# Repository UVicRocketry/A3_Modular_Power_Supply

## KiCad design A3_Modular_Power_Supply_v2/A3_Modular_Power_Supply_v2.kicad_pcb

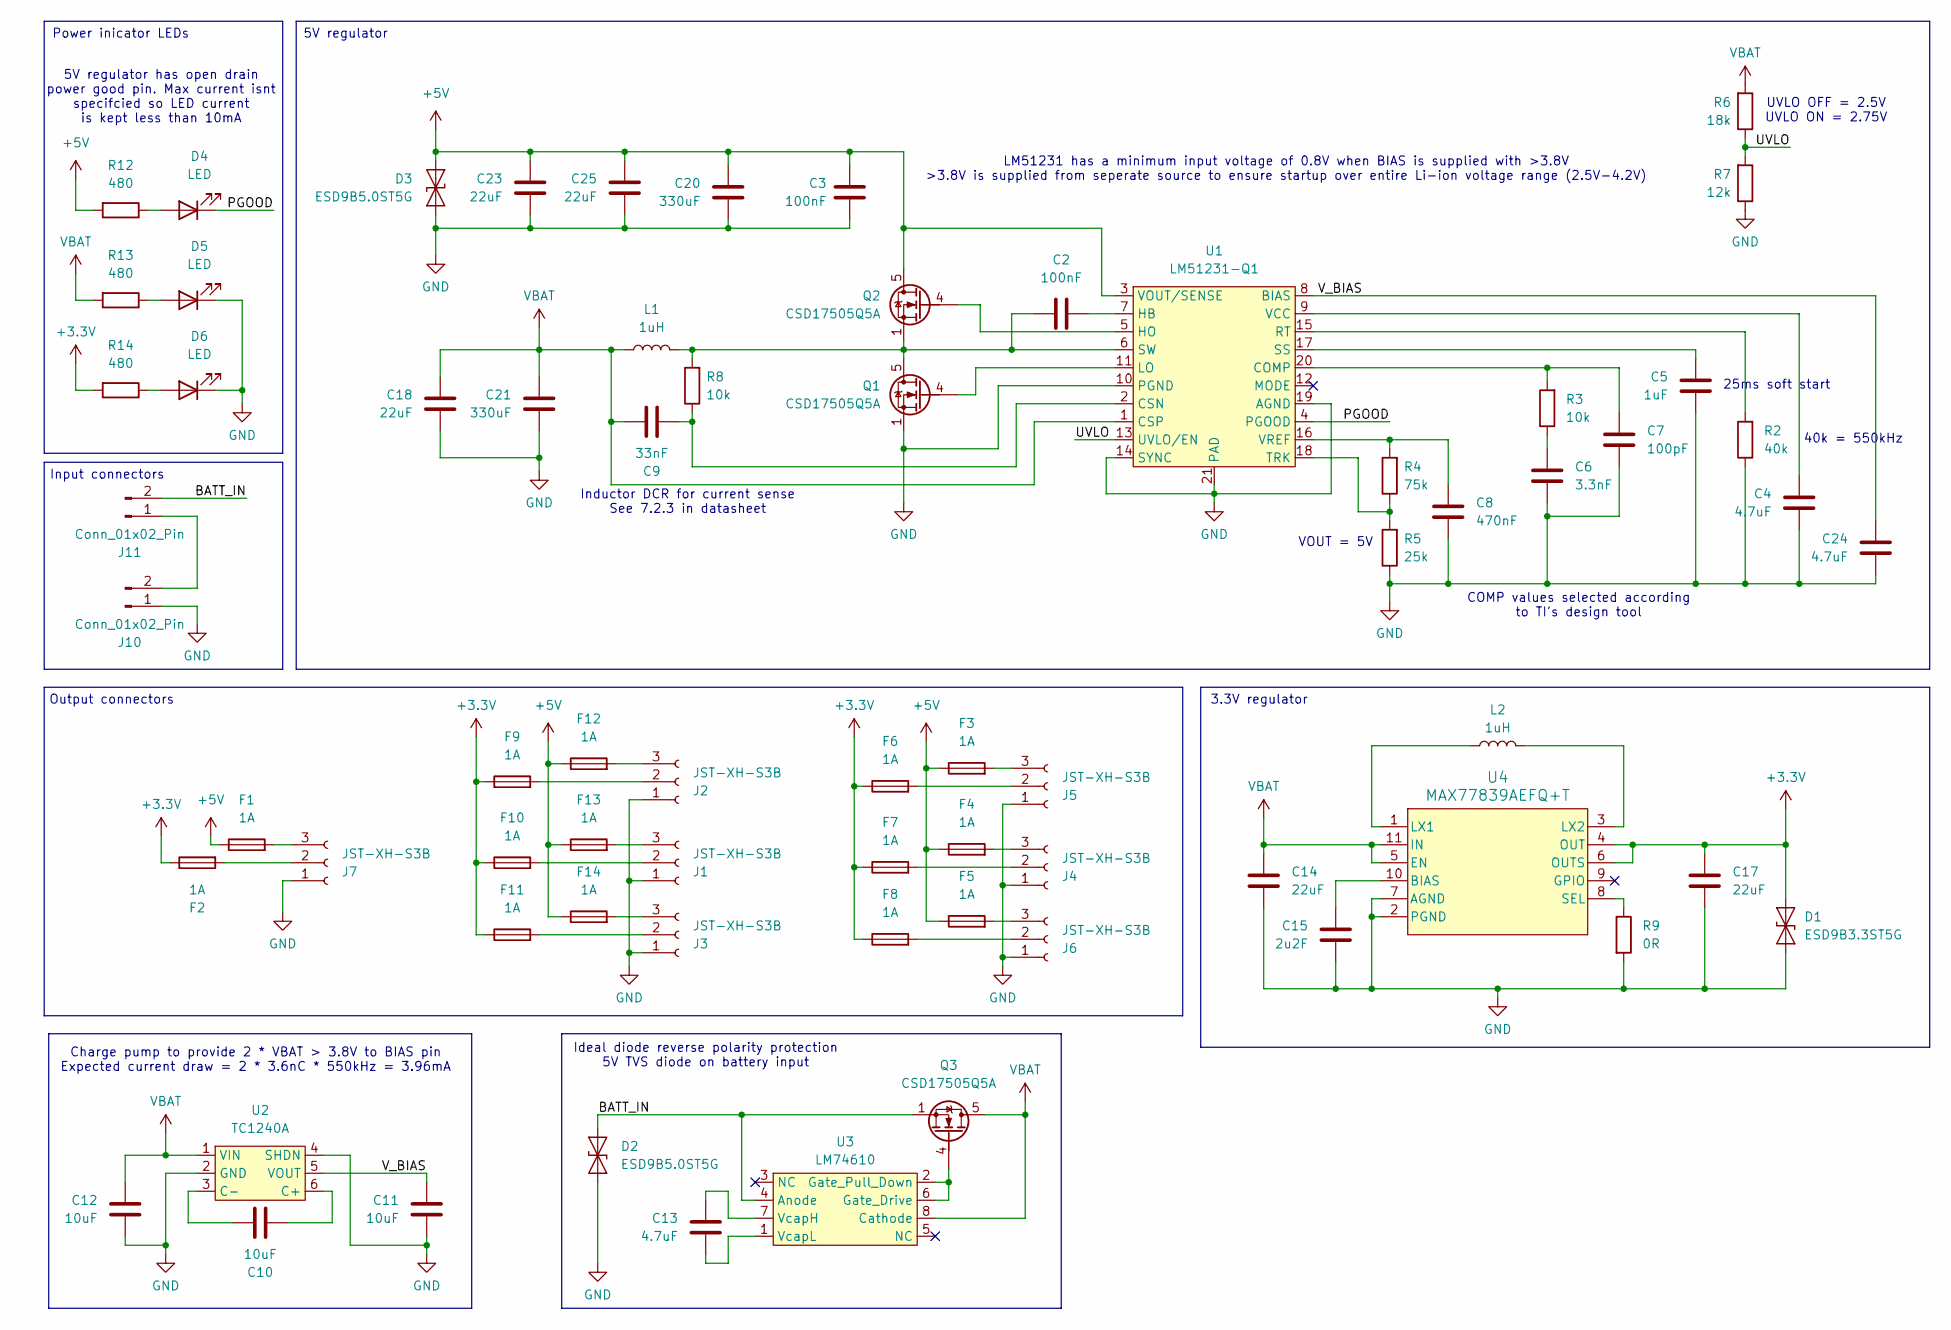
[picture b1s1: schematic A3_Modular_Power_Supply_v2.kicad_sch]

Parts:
C2, C3: 100nF; C_0402_1005Metric
C4, C13, C24: 4.7uF; C_0603_1608Metric
C5: 1uF; C_0402_1005Metric
C6: 3.3nF; C_0402_1005Metric
C7: 100pF; C_0402_1005Metric
C8: 470nF; C_0402_1005Metric
C9: 33nF; C_0402_1005Metric
C10, C11, C12: 10uF; C_0603_1608Metric
C14, C17, C18, C23, C25: 22uF; C_1210_3225Metric
C15: 2u2F; C_0603_1608Metric
C20, C21: 330uF; CP_Elec_6.3x7.7
D1: ESD9B3.3ST5G; D_SOD-923
D2, D3: ESD9B5.0ST5G; D_SOD-923
D4, D5, D6: LED; LED_0603_1608Metric
F1, F2, F3, F4, F5, F6, F7, F8, F9, F10, F11, F12, F13, F14: 1A; Fuse_0603_1608Metric
J1, J2, J3, J4, J5, J6, J7: JST-XH-S3B; JST_XH_S3B-XH-A_1x03_P2.50mm_Horizontal
J10, J11: Conn_01x02_Pin; JST_VH_B2PS-VH_1x02_P3.96mm_Horizontal
L1: 1uH; SRP1038WA
L2: 1uH; L_Wuerth_MAPI-5020
Q1, Q2, Q3: CSD17505Q5A; TDSON-8-1
R2: 40k; R_0402_1005Metric
R3, R8: 10k; R_0402_1005Metric
R4: 75k; R_0402_1005Metric
R5: 25k; R_0402_1005Metric
R6: 18k; R_0402_1005Metric
R7: 12k; R_0402_1005Metric
R9: 0R; R_0402_1005Metric
R12, R13, R14: 480; R_0402_1005Metric
U1: LM51231-Q1; QFN-20-1EP_3.5x3.5mm_P0.5mm_EP2x2mm
U2: TC1240A; TSOT-23-6
U3: LM74610; VSSOP-8_3x3mm_P0.65mm
U4: MAX77839AEFQ+T; 21-100431_F112A2F&plus_1_MXM

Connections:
+3.3V: C17.1, D1.2 (A2), F2.1, F6.1, F7.1, F8.1, F9.1, F10.1, F11.1, R14.2, U4.4 (OUT), U4.6 (OUTS)
+5V: C3.2, C20.1, C23.1, C25.1, D3.2 (A2), F1.1, F3.1, F4.1, F5.1, F12.1, F13.1, F14.1, Q2.5 (D), R12.2, U1.3 (VOUT/SENSE)
/BATT_IN: D2.2 (A2), J11.2, Q3.1 (S), Q3.2 (S), Q3.3 (S), U3.4 (Anode)
/PGOOD: D4.1 (K), U1.4 (PGOOD)
/UVLO: R6.1, R7.2, U1.13 (UVLO/EN)
/V_BIAS: C11.1, C24.1, U1.8 (BIAS), U2.5 (VOUT)
GND: C3.1, C4.2, C5.2, C6.2, C7.2, C8.2, C11.2, C12.2, C14.2, C15.2, C17.2, C18.2, C20.2, C21.2, C23.2, C24.2, C25.2, D1.1 (A1), D2.1 (A1), D3.1 (A1), D5.1 (K), D6.1 (K), J1.1, J2.1, J3.1, J4.1, J5.1, J6.1, J7.1, J10.1, Q1.1 (S), Q1.2 (S), Q1.3 (S), R2.1, R5.1, R7.1, R9.2, U1.10 (PGND), U1.14 (SYNC), U1.19 (AGND), U1.21 (PAD), U2.2 (GND), U2.4 (SHDN), U4.2 (PGND), U4.7 (AGND)
unnamed: C6.1, R3.1
unnamed: D4.2 (A), R12.1
unnamed: D5.2 (A), R13.1
unnamed: D6.2 (A), R14.1
unnamed: F10.2, J1.2
unnamed: F13.2, J1.3
unnamed: F9.2, J2.2
unnamed: F12.2, J2.3
unnamed: F11.2, J3.2
unnamed: F14.2, J3.3
unnamed: F7.2, J4.2
unnamed: F4.2, J4.3
unnamed: F6.2, J5.2
unnamed: F3.2, J5.3
unnamed: F8.2, J6.2
unnamed: F5.2, J6.3
unnamed: F2.2, J7.2
unnamed: F1.2, J7.3
unnamed: J10.2, J11.1
unnamed: C2.1, L1.2, Q1.5 (D), Q2.1 (S), Q2.2 (S), Q2.3 (S), R8.2, U1.6 (SW)
unnamed: Q1.4 (G), U1.11 (LO)
unnamed: Q2.4 (G), U1.5 (HO)
unnamed: Q3.4 (G), U3.2 (Gate_Pull_Down), U3.6 (Gate_Drive)
unnamed: C7.1, R3.2, U1.20 (COMP)
unnamed: C9.1, R8.1, U1.2 (CSN)
unnamed: C2.2, U1.7 (HB)
unnamed: R2.2, U1.15 (RT)
unnamed: C5.1, U1.17 (SS)
unnamed: R4.1, R5.2, U1.18 (TRK)
unnamed: C4.1, U1.9 (VCC)
unnamed: C8.1, R4.2, U1.16 (VREF)
unnamed: C10.1, U2.6 (C+)
unnamed: C10.2, U2.3 (C-)
unnamed: C13.1, U3.7 (VcapH)
unnamed: C13.2, U3.1 (VcapL)
unnamed: C15.1, U4.10 (BIAS)
unnamed: L2.1, U4.1 (LX1)
unnamed: L2.2, U4.3 (LX2)
unnamed: R9.1, U4.8 (SEL)
VBAT: C9.2, C12.1, C14.1, C18.1, C21.1, L1.1, Q3.5 (D), R6.2, R13.2, U1.1 (CSP), U2.1 (VIN), U3.8 (Cathode), U4.5 (EN), U4.11 (IN)

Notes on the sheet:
5V regulator has open drain power good pin. Max current isnt specifcied so LED current is kept less than 10mA
VOUT = 5V
COMP values selected according to TI's design tool
Inductor DCR for current sense See 7.2.3 in datasheet
Charge pump to provide 2 * VBAT > 3.8V to BIAS pin Expected current draw = 2 * 3.6nC * 550kHz = 3.96mA
Input connectors
Power inicator LEDs
LM51231 has a minimum input voltage of 0.8V when BIAS is supplied with >3.8V >3.8V is supplied from seperate source to ensure startup over entire Li-ion voltage range (2.5V-4.2V)
Ideal diode reverse polarity protection 5V TVS diode on battery input
40k = 550kHz
UVLO OFF = 2.5V UVLO ON = 2.75V
25ms soft start
3.3V regulator
Output connectors
5V regulator

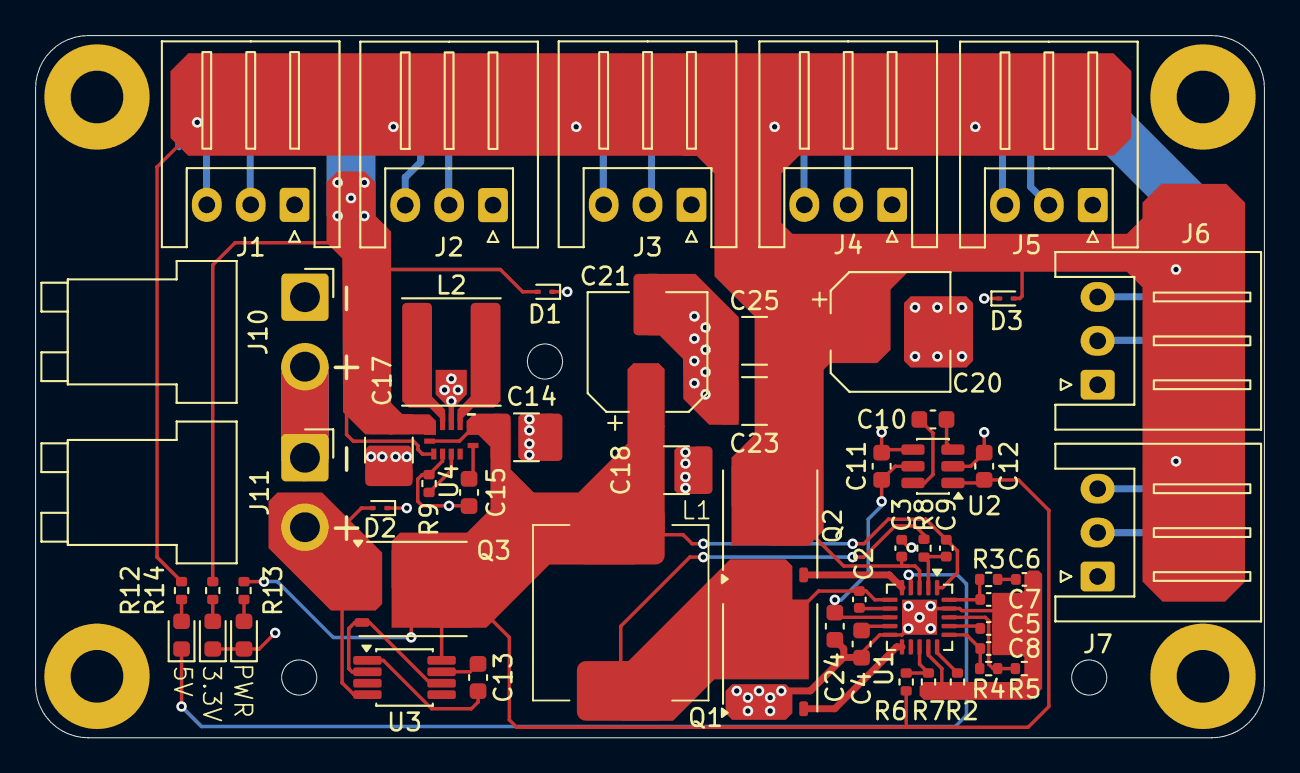
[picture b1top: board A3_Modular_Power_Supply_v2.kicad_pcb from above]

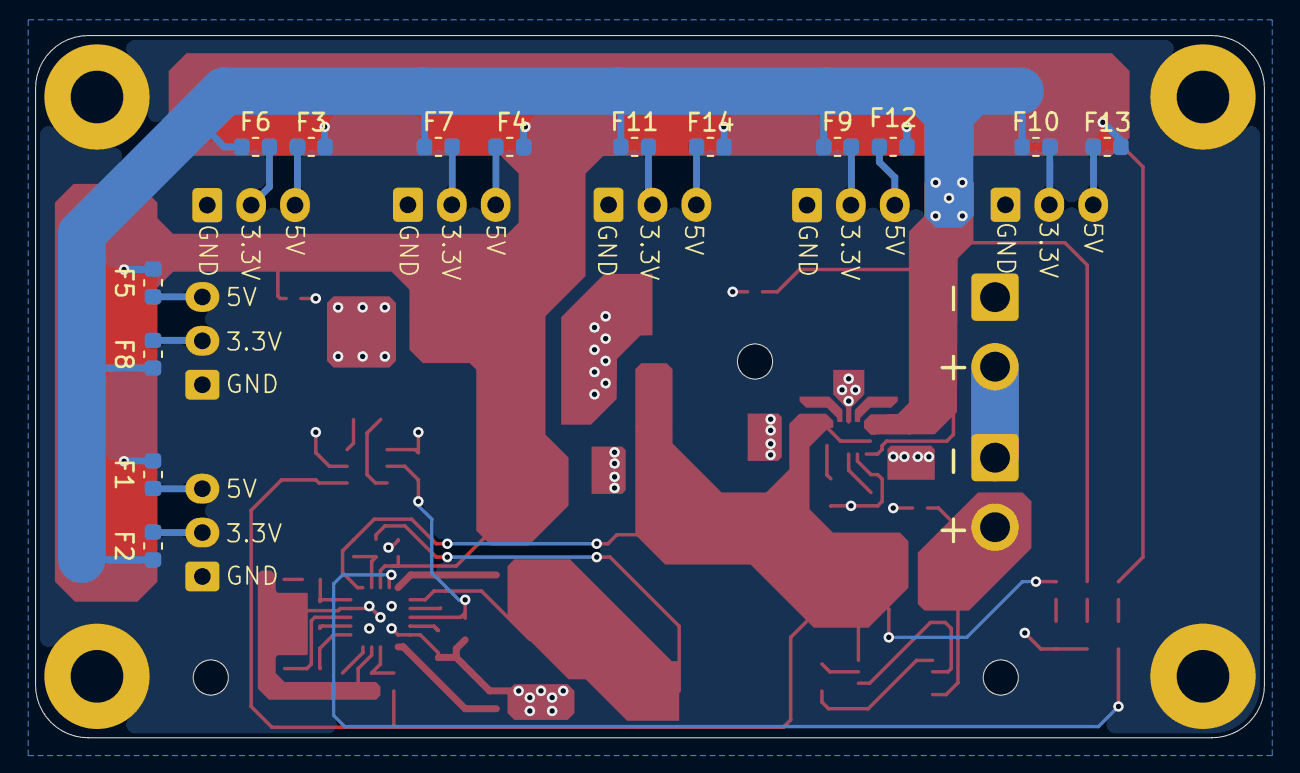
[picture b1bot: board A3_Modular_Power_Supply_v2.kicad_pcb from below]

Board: 2 copper layers, 70.0 x 40.0 mm, 70 parts (14 on the bottom side), 47 nets.

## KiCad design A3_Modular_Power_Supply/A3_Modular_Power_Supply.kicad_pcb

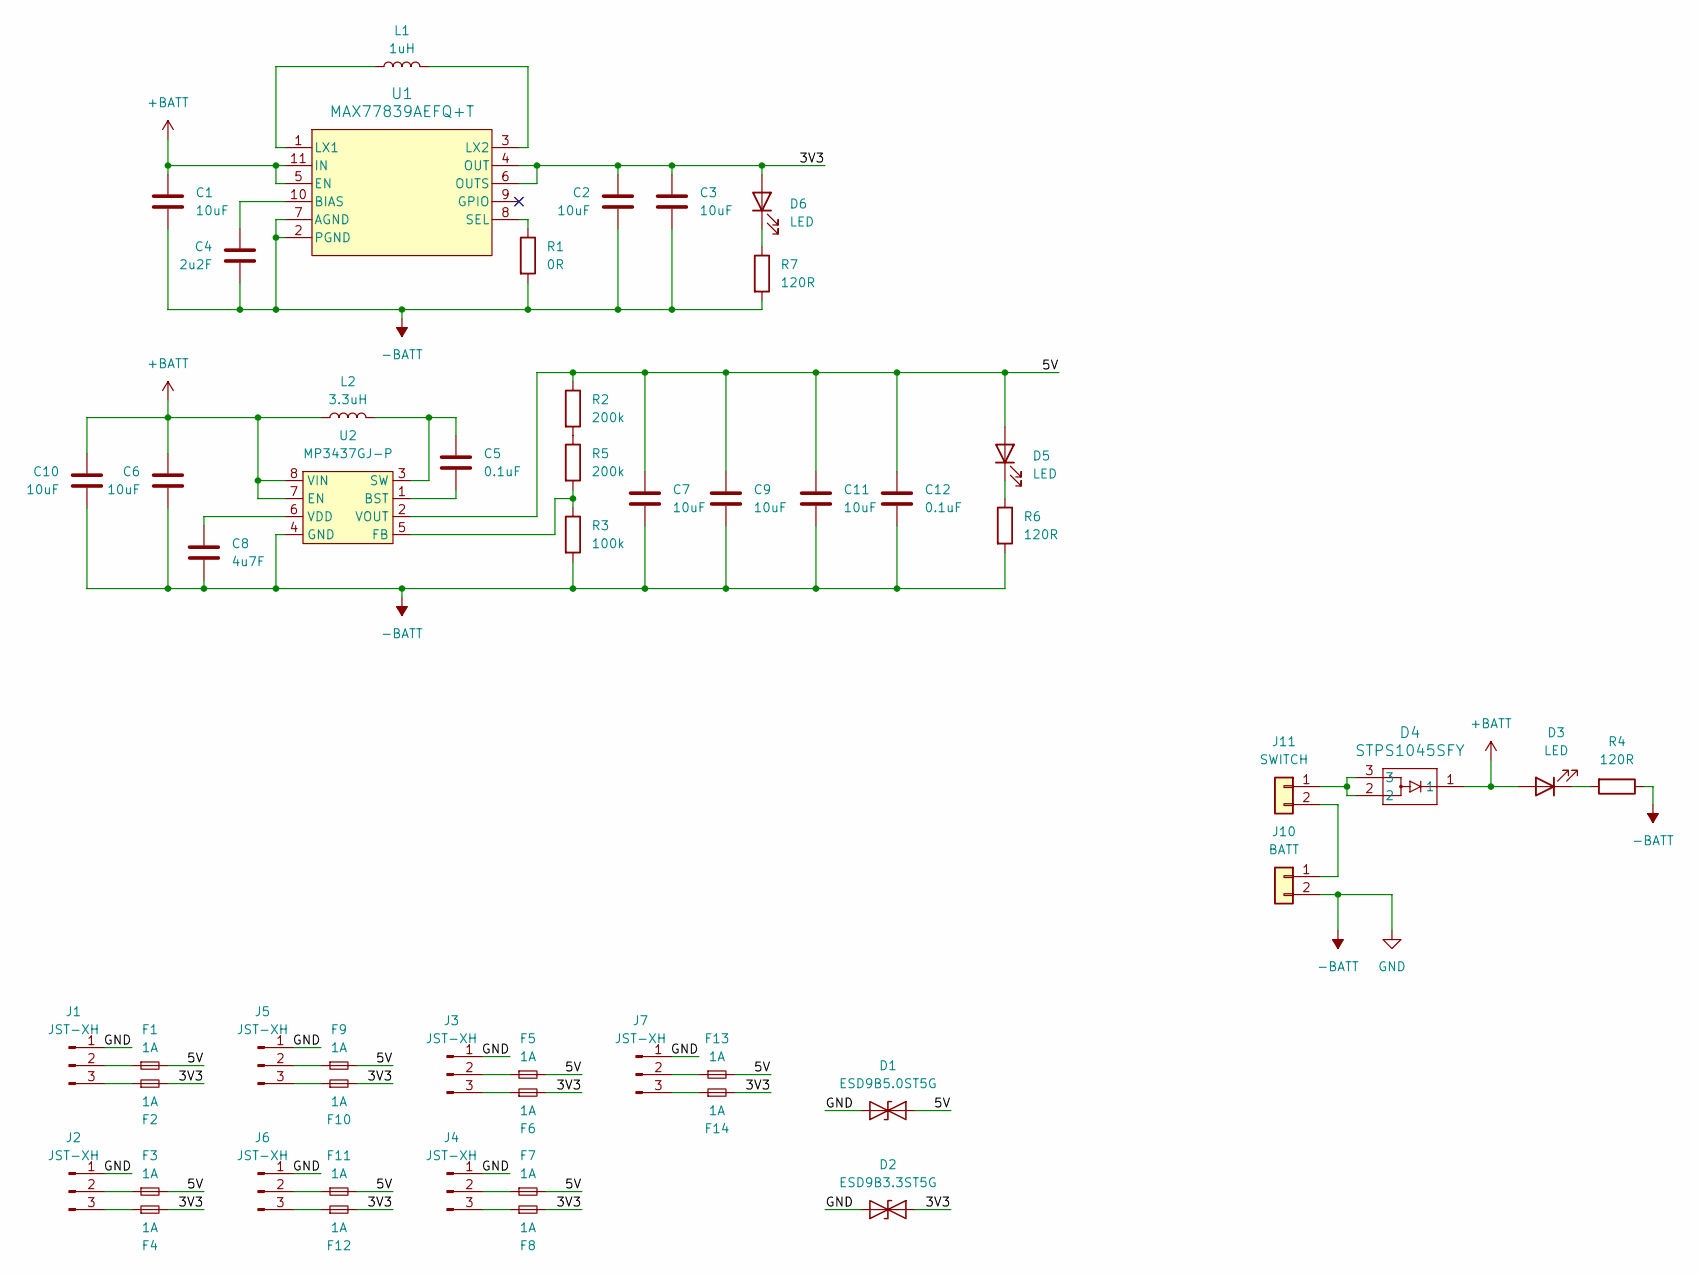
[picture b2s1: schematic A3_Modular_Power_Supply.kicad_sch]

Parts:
C1, C2, C3, C6, C7, C9, C10, C11: 10uF; C_1206_3216Metric
C4: 2u2F; C_0805_2012Metric
C5, C12: 0.1uF; C_0603_1608Metric
C8: 4u7F; C_0603_1608Metric
D1: ESD9B5.0ST5G; D_SOD-923
D2: ESD9B3.3ST5G; D_SOD-923
D3, D5, D6: LED; LED_0603_1608Metric
D4: STPS1045SFY; PSMCTO-277A_STM
F1, F2, F3, F4, F5, F6, F7, F8, F9, F10, F11, F12, F13, F14: 1A; Fuse_0603_1608Metric
J1, J2, J3, J4, J5, J6, J7: JST-XH; JST_XH_S3B-XH-A_1x03_P2.50mm_Horizontal
J10: BATT; JST_VH_B2PS-VH_1x02_P3.96mm_Horizontal
J11: SWITCH; JST_VH_B2PS-VH_1x02_P3.96mm_Horizontal
L1: 1uH; L_Wuerth_MAPI-5020
L2: 3.3uH; L_Wurth_WE-XHMI-6060P
R1: 0R; R_0603_1608Metric
R2, R5: 200k; R_0603_1608Metric
R3: 100k; R_0603_1608Metric
R4, R6, R7: 120R; R_0603_1608Metric
U1: MAX77839AEFQ+T; 21-100431_F112A2F&plus_1_MXM
U2: MP3437GJ-P

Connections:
+BATT: C1.1, C6.1, C10.1, D3.2 (A), D4.1, L2.1, U1.5 (EN), U1.11 (IN), U2.7 (EN), U2.8 (VIN)
-BATT: C1.2, C2.2, C3.2, C4.2, C6.2, C7.2, C8.2, C9.2, C10.2, C11.2, C12.2, D1.2 (A2), D2.1 (A1), J1.1, J2.1, J3.1, J4.1, J5.1, J6.1, J7.1, J10.2, R1.2, R3.2, R4.1, R6.2, R7.2, U1.2 (PGND), U1.7 (AGND), U2.4 (GND)
/3V3: C2.1, C3.1, D2.2 (A2), D6.2 (A), F2.2, F4.2, F6.2, F8.2, F10.2, F12.2, F14.2, U1.4 (OUT), U1.6 (OUTS)
/5V: C7.1, C9.1, C11.1, C12.1, D1.1 (A1), D5.2 (A), F1.2, F3.2, F5.2, F7.2, F9.2, F11.2, F13.2, R2.1, U2.2 (VOUT)
unnamed: D3.1 (K), R4.2
unnamed: D5.1 (K), R6.1
unnamed: D6.1 (K), R7.1
unnamed: F1.1, J1.2
unnamed: F2.1, J1.3
unnamed: F3.1, J2.2
unnamed: F4.1, J2.3
unnamed: F5.1, J3.2
unnamed: F6.1, J3.3
unnamed: F7.1, J4.2
unnamed: F8.1, J4.3
unnamed: F9.1, J5.2
unnamed: F10.1, J5.3
unnamed: F11.1, J6.2
unnamed: F12.1, J6.3
unnamed: F13.1, J7.2
unnamed: F14.1, J7.3
unnamed: J10.1, J11.2
unnamed: D4.2, D4.3, J11.1
unnamed: R2.2, R5.1
unnamed: C4.1, U1.10 (BIAS)
unnamed: L1.1, U1.1 (LX1)
unnamed: L1.2, U1.3 (LX2)
unnamed: R1.1, U1.8 (SEL)
unnamed: C5.2, U2.1 (BST)
unnamed: R3.1, R5.2, U2.5 (FB)
unnamed: C5.1, L2.2, U2.3 (SW)
unnamed: C8.1, U2.6 (VDD)

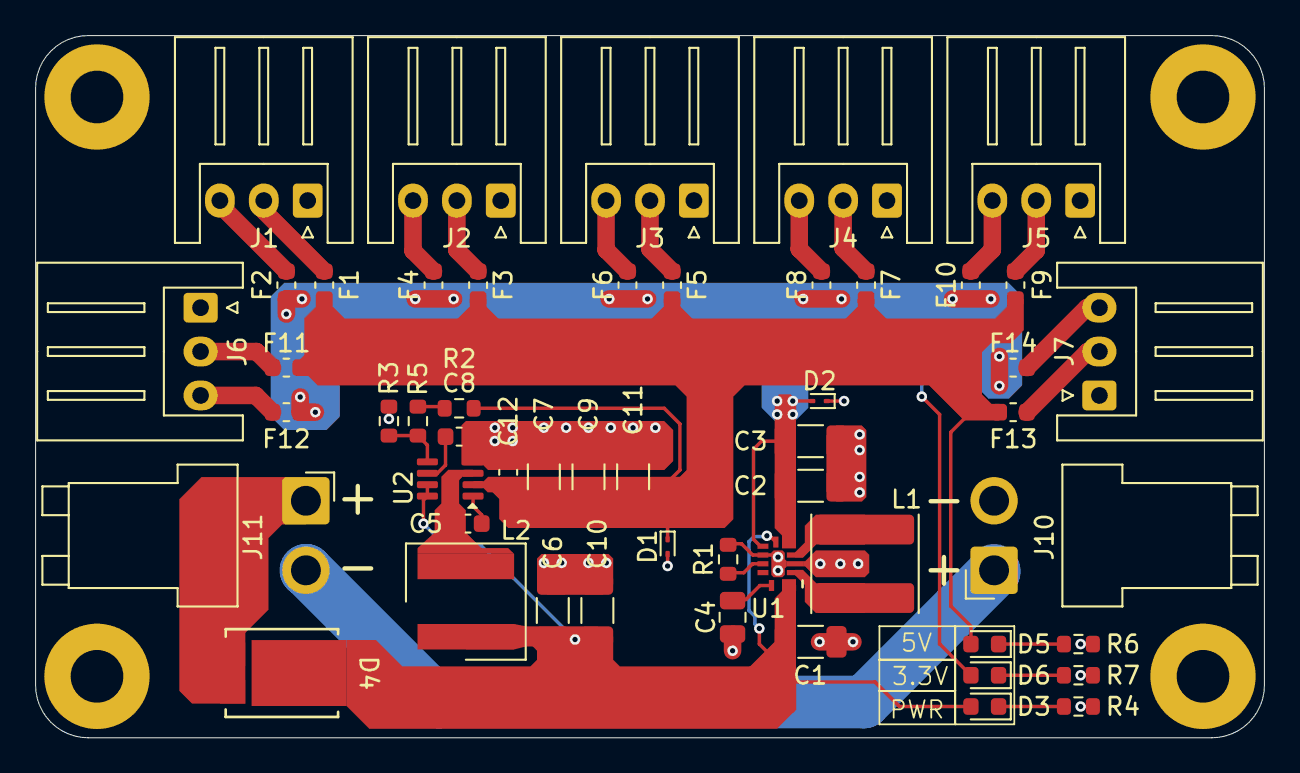
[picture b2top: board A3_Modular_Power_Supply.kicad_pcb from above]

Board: 2 copper layers, 70.0 x 40.0 mm, 52 parts (0 on the bottom side), 32 nets.

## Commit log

2025-11-14 Removed lock file.
2025-12-09 Resized board to match flight computer Switched to single PCB
2026-01-04 Added power indication LEDs
2026-06-01 Version 2 schematic and PCB
2026-06-01 Changed some capacitor package sizes
2026-06-02 Connector labels, heatsink mounting
